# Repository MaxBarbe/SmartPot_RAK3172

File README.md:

# SmartPot — pot de fleur connecté LoRaWAN 868 MHz

Projet de **Maxime — [MaxBarbe](https://github.com/MaxBarbe)**, développé dans le cadre du Master M2 : carte RAK3172, gestion d’énergie BQ25570, capteur SHT40, antenne imprimée et pot modélisé en 3D.

**Mise à jour du 28 octobre 2026.** La carte KiCad actuelle est la **V4 quatre couches**. Sa reconstruction CST avec excitation côté radio a produit un premier résultat M2 : **S11 = −8,97 dB à 868 MHz**. La convergence du maillage reste à démontrer. Une **V5 d’adaptation existe dans CST**, sans résultat publié à ce stade et sans modification de l’assemblage KiCad V4.

[Projet KiCad V4](pot_fleur_v4_nouvelle_antenne/pot_fleur.kicad_pro) · [PCB](pot_fleur_v4_nouvelle_antenne/pot_fleur.kicad_pcb) · [Simulation V4 M2](CST/V4_U112_868/README.md) · [Proposition V5](CST/V5_ADAPTATION_868/README.md) · [Anciennes versions](old/README.md)

## Carte V4 en 3D et intégration mécanique

<table>
<tr>
<td align="center" width="50%"><br><strong>V4 — carte routée, nouvelle antenne</strong></td>
<td align="center" width="50%"><br><strong>Pot — étude d’intégration mécanique</strong><br>Cette capture d’assemblage précède la V4.</td>
</tr>
</table>

[Carte V4 STEP](pot_fleur_v4_nouvelle_antenne/3D/SmartPot_V4_RF_provisoire.step) · [Carte V4 GLB](pot_fleur_v4_nouvelle_antenne/3D/SmartPot_V4_RF_provisoire.glb) · [Pot 3MF](Mecanique/Pot_fleur/Pot_fleur.3mf) · [Pot STL](Mecanique/Pot_fleur/Pot_fleur.stl)

La carte mesure **30 × 60 × 0,8 mm**, avec connecteurs latéraux, deux trous de fixation et emplacements RF en **0603**. Le cuivre d’antenne reste sans vernis. Les modèles mécaniques sont disponibles pour vérifier l’encombrement ; ils ne remplacent pas les modèles électromagnétiques CST.

## Routage et contrôles KiCad

| Contrôle enregistré sur la V4 | Résultat |
|---|---:|
| Violations DRC | **0** |
| Connexions manquantes | **0** |
| Défauts de parité schéma / PCB | **0** |
| Segments / vias traversants | 415 / 204 |
| Empilage fabricant confirmé | **Non** |
| Validation RF / fabrication | **En cours** |

[Vue du routage](pot_fleur_v4_nouvelle_antenne/docs/V4_routee.svg) · [Rapport DRC](pot_fleur_v4_nouvelle_antenne/docs/DRC_V4_routee.json) · [Audit piste par piste](pot_fleur_v4_nouvelle_antenne/docs/Audit_pistes_V4.csv) · [Export ODB++ V4](pot_fleur_v4_nouvelle_antenne/CST_import/SmartPot_V4_RF_PROVISOIRE_ODB.zip)

La branche supérieure de l’antenne est conservée en position **X0**, sans le décalage de +0,40 mm de l’essai historique. La piste RF a une largeur de **0,229278 mm**, calculée pour un empilage provisoire : cuivre 35 µm, FR4 εr = 4,3, distance F.Cu/In1.Cu de 0,127 mm. Les 50 Ω du trajet réel restent à vérifier avec l’empilage fabricant et les discontinuités des composants. Un DRC sans erreur ne démontre ni l’adaptation ni le rendement de l’antenne.

## Simulation de la carte V4 — résultat provisoire M2

Le modèle est reconstruit depuis le cuivre routé V4, avec quatre couches, plans, vias et raccord physique vers l’antenne. Le **port 50 Ω est à U1.12 vers GND In1**. Le long port du premier modèle d’antenne n’est pas réutilisé à travers la piste physique.

| Grandeur à 868 MHz | V4 M2 |
|---|---:|
| S11 | **−8,96572 dB** |
| Impédance d’entrée au port | **23,755 + j1,301 Ω** |
| Minimum échantillonné | −9,02577 dB à 868,9 MHz |
| Rendement de rayonnement simulé | 43,69 % |
| Rendement total simulé | 38,14 % |
| Gain réalisé maximal simulé | −2,400 dBi |
| Maillage | 770 308 cellules |
| Bande calculée | 700–1 000 MHz |
| Critère d’énergie −50 dB | Atteint |
| Convergence spatiale | **Non démontrée** |

M1 donnait −0,02676 dB à 868 MHz avec 205 387 cellules. L’écart M1/M2 reste trop grand pour annoncer un résultat convergé. M3 est préparé à 959 112 cellules, mais aucun résultat M3 n’est publié. L’objectif **S11 ≤ −14 dB à 868 MHz n’est pas atteint** dans la V4 M2 ; aucune bande sous −10 dB n’est obtenue dans la plage simulée.

[Compte rendu et limites](CST/V4_U112_868/README.md) · [Projet M2 et résultats natifs](CST/V4_U112_868/modeles/SmartPot_V4_U112_TD_M2_2019.zip) · [Exports numériques et Touchstone](CST/V4_U112_868/resultats/) · [Comparaison de maillage](CST/V4_U112_868/audits/mesh_comparison.json)

## V5 CST — adaptation proposée, résultat non publié

La V5 est une **variante de simulation dérivée de la V4 M2**, pas une nouvelle carte KiCad validée. Elle conserve la géométrie et le port côté radio, et propose :

| Emplacement | V4 KiCad actuelle | Proposition V5 CST |
|---|---|---|
| R4 | 0 Ω monté | Liaison 0 Ω conservée |
| R6 | 0 Ω monté | Inductance série idéale **4,3 nH** |
| C6 | DNP | Condensateur shunt idéal **3,9 pF** |
| L1 / J3 | DNP | DNP |

L’objectif V5 est **S11 ≤ −16 dB à 868 MHz**. Le modèle publié a 807 240 cellules et deux éléments L/C idéaux ; son calcul a été lancé le 28 octobre à 14 h 08, heure de Paris. **Aucun résultat V5 n’est fourni dans le dernier commit récupéré : aucun gain d’adaptation n’est annoncé.** Les valeurs ne sont pas appliquées à la nomenclature KiCad V4 en l’absence de validation. Les parasites et pertes des composants réels devront être considérés.

[Documentation V5](CST/V5_ADAPTATION_868/README.md) · [Projet CST V5](CST/V5_ADAPTATION_868/modeles/SmartPot_V5_R6L4p3_C6C3p9_TD_M2_2019.zip) · [Audit de l’adaptation](CST/V5_ADAPTATION_868/audits/SmartPot_V5_R6L4p3_C6C3p9_TD_M2_2019_matching_audit.txt)

## Référence X0 et anciennes versions

Le point **−11,020993 dB à 868 MHz** concerne le modèle d’antenne X0 à port lumped, en fréquentiel avec cuivre PEC. Il a servi au choix de géométrie, mais ne constitue pas le résultat de la V4 alimentée depuis la radio. [Référence X0 et essai X +0,40 mm](CST/ANTENNE_868_3QUARTS/README.md).

Les cartes KiCad V1/V2/V3 et les anciens projets CST sont regroupés dans **[old/](old/README.md)**. Leurs courbes, rapports et fichiers restent disponibles pour comparaison. Les références pédagogiques sont conservées dans [references/EDU_RAK_2026](references/EDU_RAK_2026/README.md).

## Reprendre le projet

1. Récupérer le dépôt à jour : `git clone https://github.com/MaxBarbe/SmartPot_RAK3172.git`, ou `git pull --ff-only` sur une copie existante sans modifications locales.
2. Dans KiCad, ouvrir `pot_fleur_v4_nouvelle_antenne/pot_fleur.kicad_pro` ; les bibliothèques utilisent `${KIPRJMOD}`.
3. Sous Windows/CST 2019, extraire entièrement l’archive du modèle V4 M2 ou de la variante V5. Conserver le `.cst` avec son dossier compagnon, puis lire la documentation du modèle.
4. Poursuivre l’étude de convergence, confirmer l’empilage fabricant et obtenir la revue des enseignants avant fabrication. Les mesures au VNA et de rayonnement sur prototype compléteront la validation.

[État détaillé](docs/ETAT_DU_PROJET.md) · [Galerie](docs/GALERIE.md) · [Origine du projet](CREDITS.md)

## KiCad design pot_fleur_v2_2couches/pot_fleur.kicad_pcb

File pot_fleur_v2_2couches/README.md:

# SmartPot V2 — PCB à deux couches

Version alternative créée le **14 octobre 2026**. Ouvrir [pot_fleur.kicad_pro](pot_fleur.kicad_pro) dans KiCad. La version quatre couches reste dans `../pot_fleur/`.

Le PCB conserve **30 × 60 × 0,8 mm**, les 50 empreintes du projet, les connecteurs latéraux, les deux trous non métallisés Ø 3 mm et l’antenne issue de CST. Le cuivre et les pistes utilisent exclusivement **F.Cu et B.Cu**. Le capteur SHT40 U4 est placé à (73,5 ; 66,5) mm pour dégager le routage. J10 est adapté pour des fils soudés directement. Les positions des autres empreintes sont conservées, avec seulement les arrondis numériques d’export. Le réseau RF reste en 0603 ; les composants DNP conservent leur statut, notamment C22.

[Voir le routage des deux couches](docs/Routage_V2.svg) · [STEP assemblé pour la mécanique](3D/SmartPot_V2_assemble.step)

## Contrôles enregistrés

| Contrôle | Résultat |
|---|---|
| Connexions manquantes | **0** |
| Parité schéma/PCB | **0 problème** |
| DRC | **0 violation** |
| ERC | **0 erreur, 6 avertissements** |
| Couches de cuivre | **2**, F.Cu / B.Cu |

J10 conserve ses deux pastilles traversantes Ø 2,6 mm, trous métallisés Ø 1,3 mm et entraxe 5,08 mm, aux positions existantes. Le bornier est remplacé par une empreinte locale de soudure directe, sans boîtier ni modèle 3D. La pastille 1 est l’entrée positive et la pastille 2 est GND. Le marquage +/GND est ajouté. Le schéma conserve le repère P-MFC de cette entrée ; aucun changement électrique n’est apporté. Le conflit de zone d’occupation H1/J10 disparaît avec l’emprise réelle des pastilles. Aucun contrôle n’a été masqué. Prévoir le passage et la tenue mécanique des fils hors de la tête de vis. Voir les rapports [DRC texte](docs/DRC_V2.txt), [DRC JSON](docs/DRC_V2.json) et [ERC](docs/ERC_V2.txt).

## Paramètres à transmettre au fabricant

- Pistes : minimum **0,15 mm** ; isolation nominale entre réseaux **0,20 mm** selon les règles du projet et les règles locales des empreintes.
- Vias traversants : **Ø 0,50 / perçage 0,30 mm** (210) et **Ø 0,40 / perçage 0,20 mm** (32). Aucun via aveugle ou microvia n’est utilisé.
- Certains vias compacts se trouvent dans des pastilles CMS, notamment pour reprendre des masses. Faire confirmer le traitement de ces vias par le fabricant : un trou ouvert peut absorber la soudure lors du montage. Le DRC ne vérifie pas ce procédé.
- Masses sur les deux faces, reliées par vias. Les pastilles CMS de masse et la masse de J10 sont reliées directement aux zones ; leur soudure peut demander davantage de chaleur.
- La zone d’exclusion de l’antenne s’applique aux deux faces.

## Validation restante

Cette V2 est un routage complet à deux couches, **pas une autorisation de fabrication**. La suppression des plans internes change le retour des courants et la structure RF. La piste d’alimentation RF de 0,20 mm n’est pas certifiée à 50 Ω sur ce PCB à deux couches de 0,8 mm. Resimuler l’antenne et son raccord dans CST avec le substrat du fabricant et l’environnement du pot ; les captures CST antérieures ne valident pas cette V2. Revoir également les boucles et découplages du BQ25570 et vérifier le passage des fils autour de H1 avant fabrication.

Les bibliothèques et modèles locaux sont inclus et utilisent `${KIPRJMOD}`. Le STEP exclut le bornier J10 et les composants DNP et contient le cuivre extérieur ; il représente la V2 et ne remplace pas le placement corrigé du pot dans Shapr3D.

## Masques et fichiers de fabrication

[Masque de vernis dessus](docs/Masque_V2_dessus.svg) · [Masque de vernis dessous](docs/Masque_V2_dessous.svg) · [Gerbers, perçages et archive](fabrication/README.md)

Les masques F.Mask/B.Mask représentent les **ouvertures du vernis**, et non les pistes de cuivre. Les Gerbers incluent également F.Paste/B.Paste pour un éventuel pochoir de pâte à braser. Ces exports sont issus de cette V2 ; les validations RF et du procédé de vias dans les pastilles restent nécessaires avant commande.

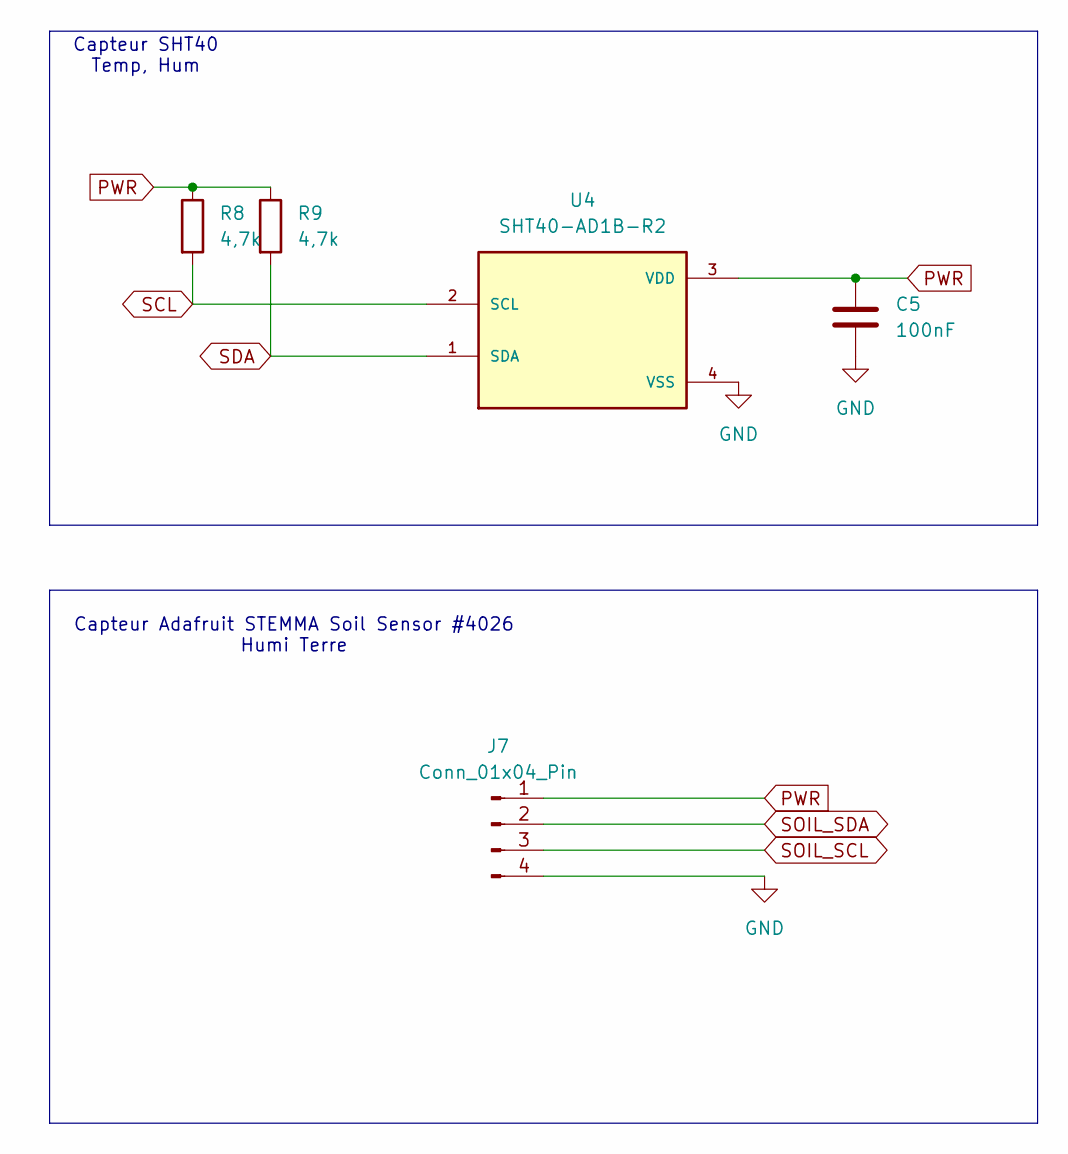
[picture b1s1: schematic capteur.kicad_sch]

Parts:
C5: 100nF; C_0603_1608Metric
J7: Conn_01x04_Pin; PinHeader_1x04_P2.54mm_Vertical
R8, R9: 4,7k; R_0603_1608Metric
U4: SHT40-AD1B-R2; SHT4X

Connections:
GND: C5.2, J7.4, U4.4 (VSS); also elsewhere on the board
PWR: C5.1, J7.1, R8.1, R9.1, U4.3 (VDD); also elsewhere on the board
SCL: J7.3, R8.2, U4.2 (SCL); also elsewhere on the board
SDA: J7.2, R9.2, U4.1 (SDA); also elsewhere on the board

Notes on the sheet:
Capteur Adafruit STEMMA Soil Sensor #4026 Humi Terre
Capteur SHT40 Temp, Hum

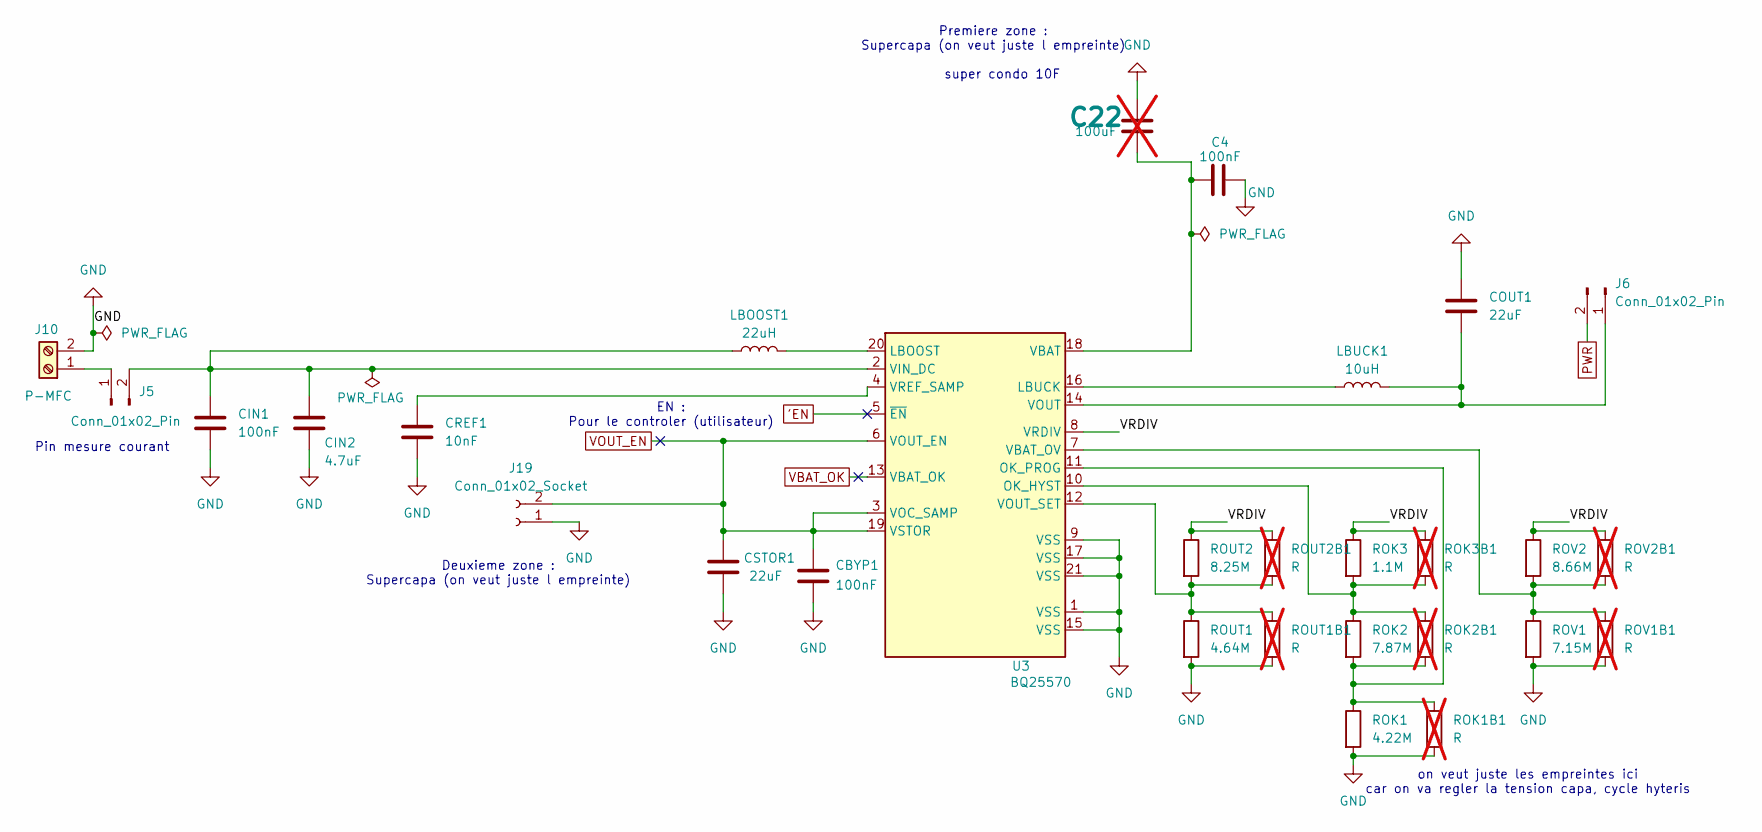
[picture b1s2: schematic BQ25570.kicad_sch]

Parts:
C4: 100nF; C_0603_1608Metric; LCSC C1591
C22: 100uF; C_0603_1608Metric; not fitted
CBYP1: 100nF; C_0603_1608Metric; LCSC C1591
CIN1: 100nF; C_0603_1608Metric; LCSC C1591
CIN2: 4.7uF; C_0603_1608Metric; LCSC C107368
COUT1: 22uF; C_0603_1608Metric; LCSC C2762594
CREF1: 10nF; C_0603_1608Metric; LCSC C1591
CSTOR1: 22uF; C_0603_1608Metric; LCSC C2762594
J5, J6: Conn_01x02_Pin; PinHeader_1x02_P2.54mm_Vertical; LCSC C3332353
J10: P-MFC; TerminalBlock_Phoenix_MKDS-3-2-5.08_1x02_P5.08mm_Horizontal; LCSC C2683165
J19: Conn_01x02_Socket; PinSocket_1x02_P2.54mm_Vertical; LCSC C5372032
LBOOST1: 22uH; IND_LPS4018-223MRC; LCSC C5441602
LBUCK1: 10uH; L_1008_2520Metric; LCSC C237599
ROK1: 4.22M; R_0603_1608Metric; LCSC C3009313
ROK1B1, ROK2B1, ROK3B1: R; R_0603_1608Metric; not fitted
ROK2: 7.87M; R_0603_1608Metric; LCSC C482913
ROK3: 1.1M; R_0603_1608Metric; LCSC C2930138
ROUT1: 4.64M; R_0603_1608Metric; LCSC C2079741
ROUT1B1, ROUT2B1: R; R_0603_1608Metric; not fitted
ROUT2: 8.25M; R_0603_1608Metric; LCSC C166757
ROV1: 7.15M; R_0603_1608Metric; LCSC C422907
ROV1B1, ROV2B1: R; R_0603_1608Metric; not fitted
ROV2: 8.66M; R_0603_1608Metric; LCSC C4087386
U3: BQ25570; QFN-20-1EP_3.5x3.5mm_P0.5mm_EP2x2mm; LCSC C506250

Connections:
'EN: U3.5 (~EN)
/BQ25570/VRDIV: ROK3.1, ROK3B1.1, ROUT2.1, ROUT2B1.1, ROV2.1, ROV2B1.1, U3.8 (VRDIV)
GND: C4.2, C22.2, CBYP1.2, CIN1.2, CIN2.2, COUT1.1, CREF1.2, CSTOR1.2, J10.2, J19.1, ROK1.2, ROK1B1.2, ROUT1.2, ROUT1B1.2, ROV1.2, ROV1B1.2, U3.1 (VSS), U3.9 (VSS), U3.15 (VSS), U3.17 (VSS), U3.21 (VSS); also elsewhere on the board
unnamed: CIN1.1, CIN2.1, J5.2, LBOOST1.1, U3.2 (VIN_DC)
unnamed: COUT1.2, J6.1, LBUCK1.2, U3.14 (VOUT)
unnamed: J5.1, J10.1
unnamed: LBOOST1.2, U3.20 (LBOOST)
unnamed: LBUCK1.1, U3.16 (LBUCK)
unnamed: ROK2.1, ROK2B1.1, ROK3.2, ROK3B1.2, U3.10 (OK_HYST)
unnamed: ROK1.1, ROK1B1.1, ROK2.2, ROK2B1.2, U3.11 (OK_PROG)
unnamed: C4.1, C22.1, U3.18 (VBAT)
unnamed: ROV1.1, ROV1B1.1, ROV2.2, ROV2B1.2, U3.7 (VBAT_OV)
unnamed: ROUT1.1, ROUT1B1.1, ROUT2.2, ROUT2B1.2, U3.12 (VOUT_SET)
unnamed: CREF1.1, U3.4 (VREF_SAMP)
PWR: J6.2; also elsewhere on the board
VBAT_OK: U3.13 (VBAT_OK)
VOUT_EN: CBYP1.1, CSTOR1.1, J19.2, U3.3 (VOC_SAMP), U3.6 (VOUT_EN), U3.19 (VSTOR)

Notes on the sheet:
on veut juste les empreintes ici car on va regler la tension capa, cycle hyteris
Premiere zone : Supercapa (on veut juste l empreinte)
super condo 10F
Deuxieme zone : Supercapa (on veut juste l empreinte)
EN : Pour le controler (utilisateur)
Pin mesure courant

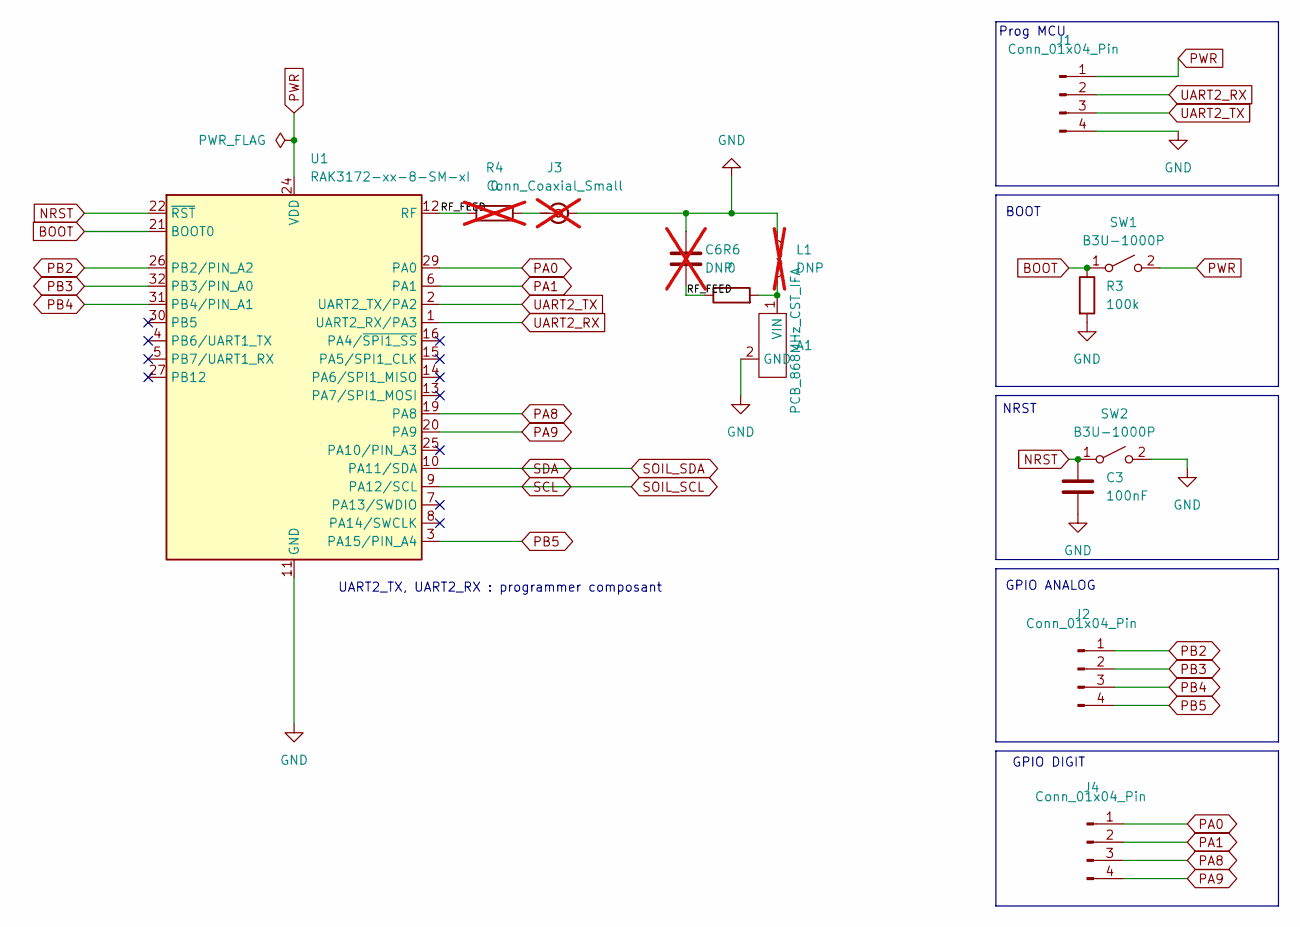
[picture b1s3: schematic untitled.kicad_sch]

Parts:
A1: PCB_868MHz_CST_IFA; CST_IFA_868MHz_SmartPot
C3: 100nF; C_0603_1608Metric
C6: DNP; C_0603_1608Metric; not fitted
J1, J2, J4: Conn_01x04_Pin; PinHeader_1x04_P2.54mm_Vertical
J3: Conn_Coaxial_Small; U.FL_Hirose_U.FL-R-SMT-1_Vertical; not fitted
L1: DNP; L_0603_1608Metric; not fitted
R3: 100k; R_0603_1608Metric
R4: 0; R_0603_1608Metric; not fitted
R6: 0; R_0603_1608Metric
SW1, SW2: B3U-1000P; SW_SPST_B3U-1000P
U1: RAK3172-xx-8-SM-xI; RAK3172

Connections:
/Microcontroleur/RF_FEED: C6.2, R4.1, R6.1, U1.12 (RF)
BOOT: R3.1, SW1.1 (A), U1.21 (BOOT0)
GND: A1.2 (GND), C3.2, C6.1, J1.4, J3.2 (Ext), L1.1, R3.2, SW2.2 (B), U1.11 (GND), U1.17 (GND), U1.18 (GND), U1.23 (GND), U1.28 (GND); also elsewhere on the board
NRST: C3.1, SW2.1 (A), U1.22 (~RST)
unnamed: A1.1 (VIN), L1.2, R6.2
unnamed: J3.1 (In), R4.2
PA0: J4.1, U1.29 (PA0)
PA1: J4.2, U1.6 (PA1)
PA8: J4.3, U1.19 (PA8)
PA9: J4.4, U1.20 (PA9)
PB2: J2.1, U1.26 (PB2/PIN_A2)
PB3: J2.2, U1.32 (PB3/PIN_A0)
PB4: J2.3, U1.31 (PB4/PIN_A1)
PB5: J2.4, U1.3 (PA15/PIN_A4)
PWR: J1.1, SW1.2 (B), U1.24 (VDD); also elsewhere on the board
SCL: U1.9 (PA12/SCL); also elsewhere on the board
SDA: U1.10 (PA11/SDA); also elsewhere on the board
UART2_RX: J1.2, U1.1 (UART2_RX/PA3)
UART2_TX: J1.3, U1.2 (UART2_TX/PA2)

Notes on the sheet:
UART2_TX, UART2_RX : programmer composant
GPIO DIGIT
Prog MCU
NRST
BOOT
GPIO ANALOG

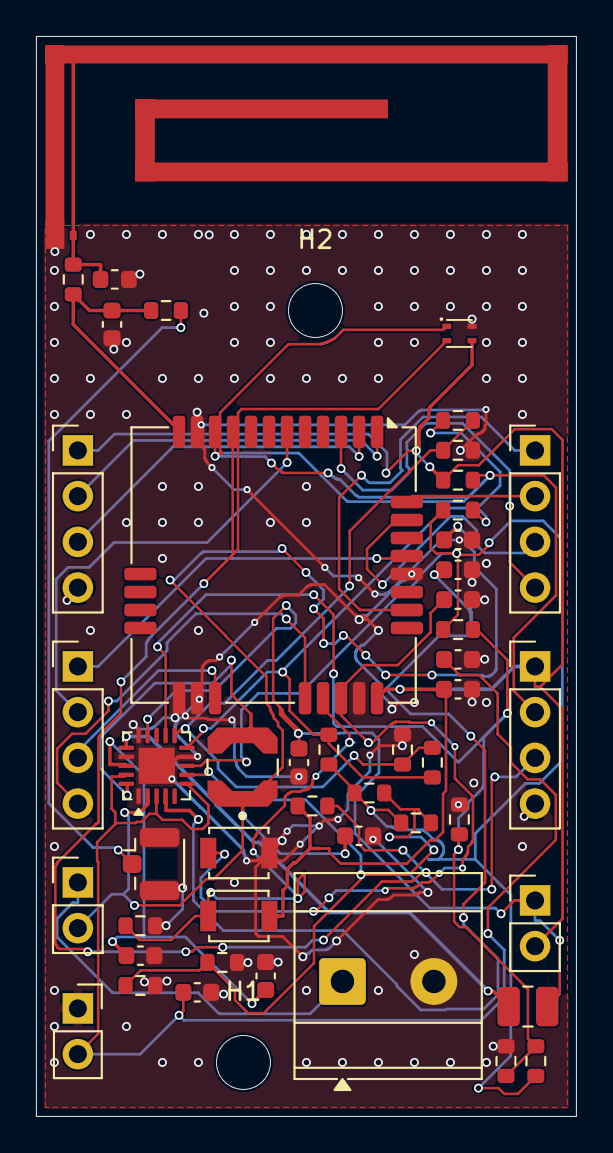
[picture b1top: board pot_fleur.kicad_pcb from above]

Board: 2 copper layers, 30.0 x 60.0 mm, 50 parts (0 on the bottom side), 32 nets.

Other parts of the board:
H1, H2: MountingHole_3mm
